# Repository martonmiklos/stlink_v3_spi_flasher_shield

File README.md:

## STLinkV3 SPI flasher shield - Untested

Drawn in EAGLE 9.x

Due to the fact that a socket and a wide SOIC8 footprint is added the signal integrity is something what we should not talk about.
If something fails use lower SPI speeds.

Socket used: cheapest SOIC socket found ebay equipped with (an obviously counterfeit) OTS-16-03 SOIC8 socket.

https://www.waveshare.com/datasheet/Test_Socket_PDF/SOP/SOP_Enplas.pdf

## Recommended flashing software

[flashrom](https://www.flashrom.org/Flashrom) supports this programmer since the 1.2 release

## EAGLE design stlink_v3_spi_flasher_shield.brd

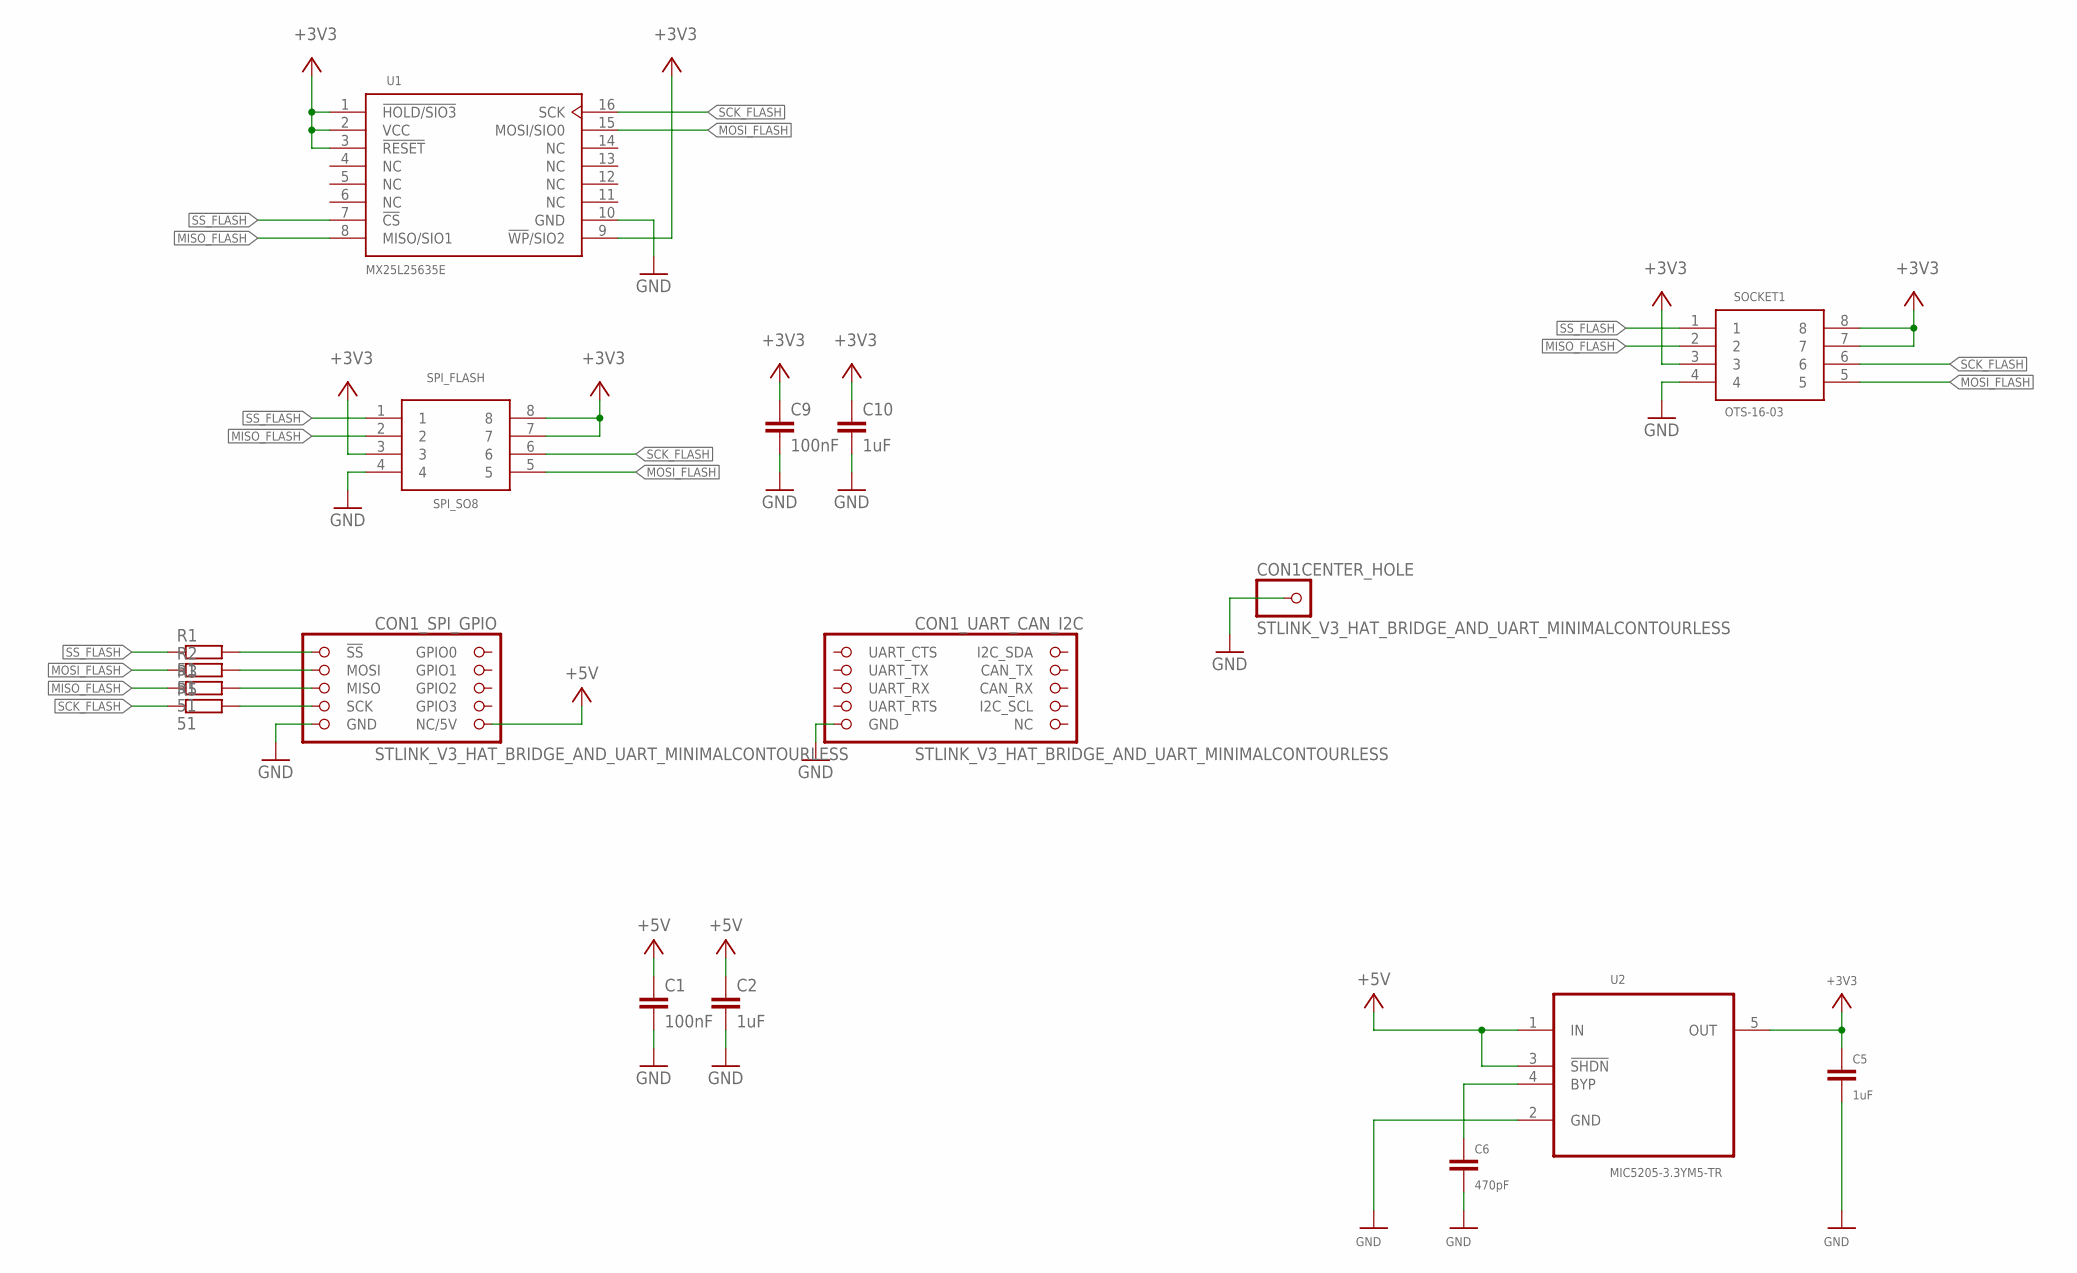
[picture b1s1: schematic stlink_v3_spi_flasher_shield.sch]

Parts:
C1, C9: 100nF; C0603
C2, C5, C10: 1uF; C0603
C6: 470pF; C0603
CON1: STLINK_V3_HAT_BRIDGE_AND_UART_MINIMALCONTOURLESS; STLINKV3_HAT_BRIDGE_MINIMAL_CONTOURLESS
R1, R2, R3, R5: 51; R0603
SOCKET1: OTS-16-03
SPI_FLASH: SPI_SO8; SO8_LONG
U1: MX25L25635E; SOP127P780X200-16N
U2: MIC5205-3.3YM5-TR; SOT95P280X145-5N

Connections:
!SS_FLASH: R1.1, SOCKET1.1, SPI_FLASH.1, U1.7 (!CS)
!SS_STLINK: CON1.SPI_1 (!SS), R1.2
+3V3: C5.1, C9.1, C10.1, SOCKET1.3, SOCKET1.7, SOCKET1.8, SPI_FLASH.3, SPI_FLASH.7, SPI_FLASH.8, U1.1 (!HOLD/SIO3), U1.2 (VCC), U1.3 (!RESET), U1.9 (!WP!/SIO2), U2.5 (OUT)
+5V: C1.1, C2.1, CON1.SPI_10 (NC/5V), U2.1 (IN), U2.3 (!SHDN)
GND: C1.2, C2.2, C5.2, C6.2, C9.2, C10.2, CON1.CENTER (1), CON1.SPI_9 (GND), CON1.UART_9 (GND), SOCKET1.4, SPI_FLASH.4, U1.10 (GND), U2.2 (GND)
MISO_FLASH: R3.1, SOCKET1.2, SPI_FLASH.2, U1.8 (MISO/SIO1)
MISO_STLINK: CON1.SPI_5 (MISO), R3.2
MOSI_FLASH: R2.1, SOCKET1.5, SPI_FLASH.5, U1.15 (MOSI/SIO0)
MOSI_STLINK: CON1.SPI_3 (MOSI), R2.2
unnamed: C6.1, U2.4 (BYP)
SCK_FLASH: R5.1, SOCKET1.6, SPI_FLASH.6, U1.16 (SCK)
SCK_STLINK: CON1.SPI_7 (SCK), R5.2

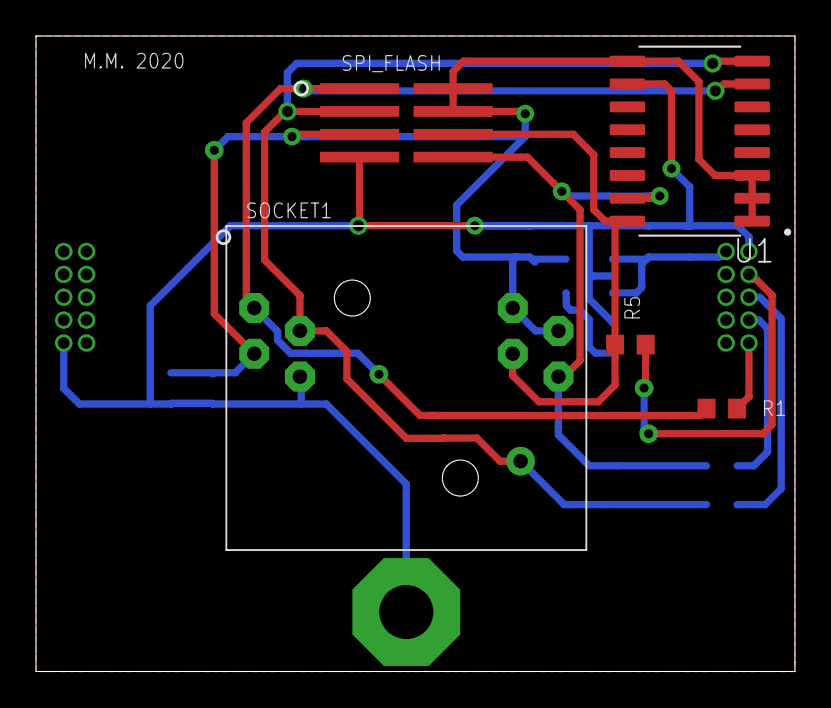
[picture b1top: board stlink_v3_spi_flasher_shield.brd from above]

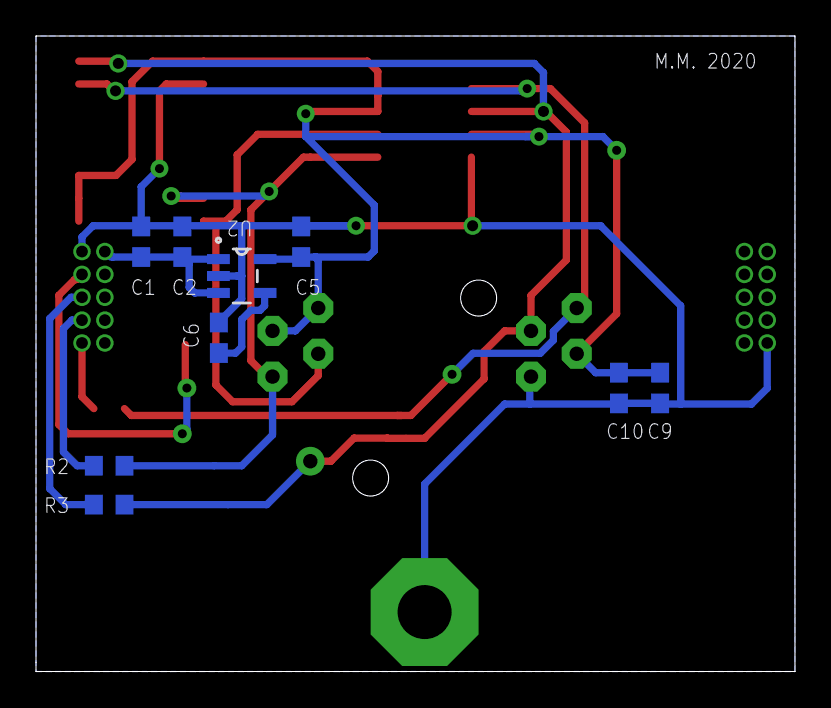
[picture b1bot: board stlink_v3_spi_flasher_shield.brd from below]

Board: 2 copper layers, 42.2 x 35.3 mm, 15 parts (9 on the bottom side), 12 nets.

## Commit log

2020-07-26 Added PCB files
2020-07-26 Signoff enforce test
2020-07-26 Signoff test #₂
2020-12-19 Added SPI socket
2020-12-19 Added readme
2023-02-26 - Added SOP16 SPI footprint - Fixup OTS socket footprint

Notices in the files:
parts and their libraries:
SparkFun: Licensing: CC v3.0 Share-Alike You are welcome to use this library for commercial purposes.
